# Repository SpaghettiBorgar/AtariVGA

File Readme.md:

# Atari to VGA Adapter
Converts VGA signals to the 13-pin DIN connector used by Atari SM/ST Series Monochrome CRT Monitors

## Features
- Adjustable R/G/B mixdown
- Adjustable output Attenuation/Amplification
- 3.5mm jack for audio passthrough
- VGA passthrough port
- 24C02 EEPROM for custom EDID
- Jumpers for SDA/SCL selection and write-protection
- Plenty of test-points for analyzing and debugging
- Blåhaj

> [!IMPORTANT]
> Some adapters will refuse to set a mode and send signals if it doesn't receive an EDID from the connected display. To provide an EDID you need to either connect a VGA monitor via the passthrough port or install and flash the 24C02 EEPROM with a valid EEPROM, preferably matching your monitor's specs as close as possible. Then use tools like `xrandr` to refine your VGA timings.

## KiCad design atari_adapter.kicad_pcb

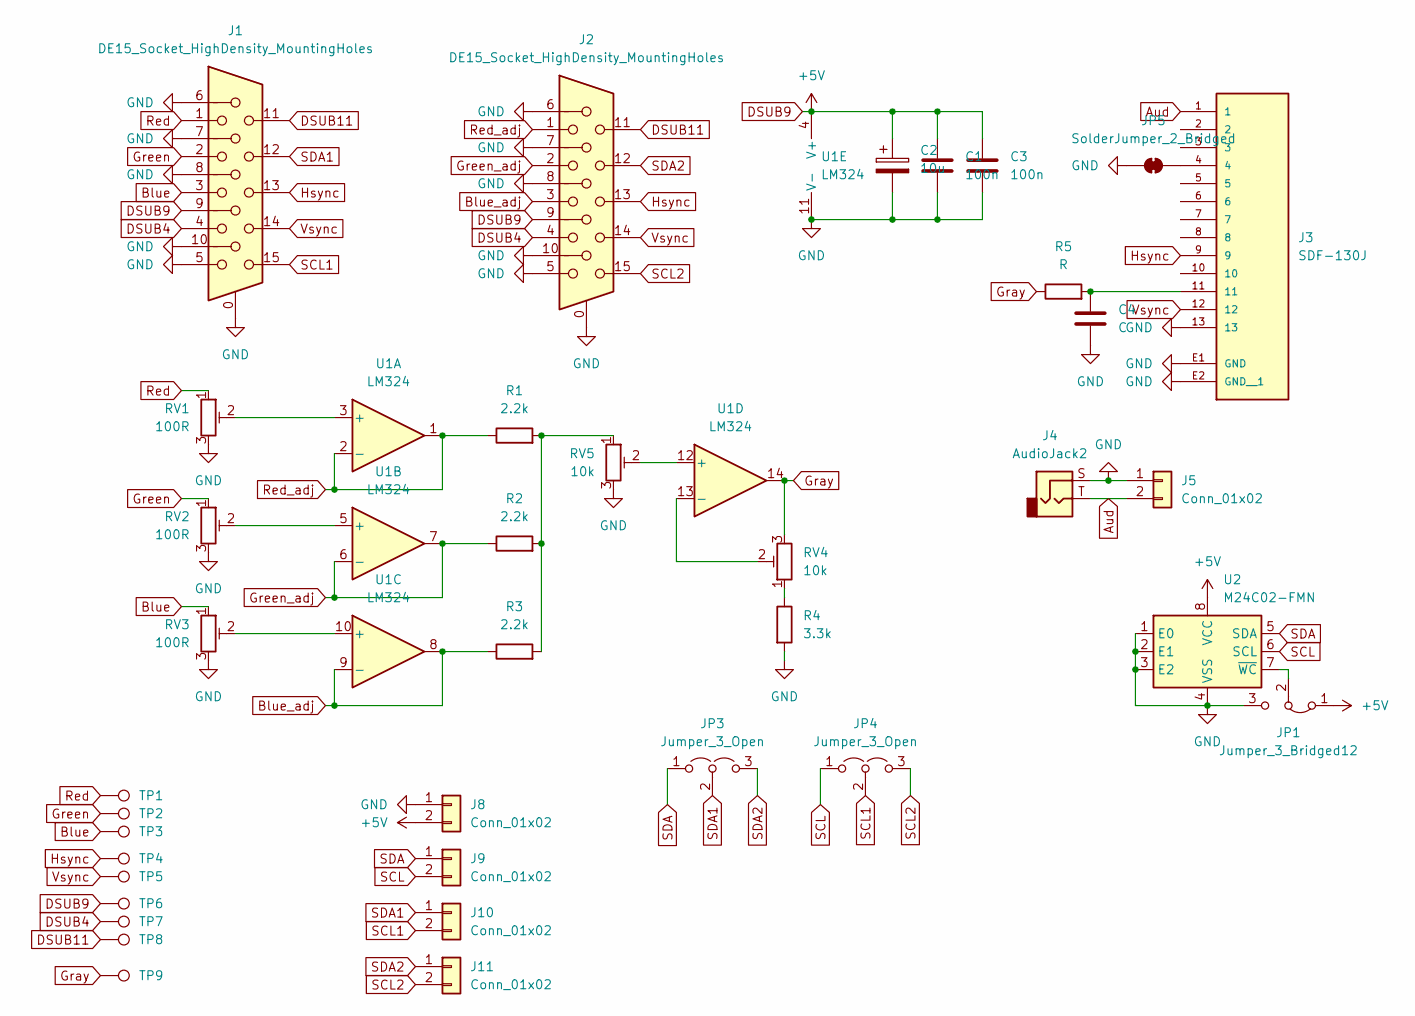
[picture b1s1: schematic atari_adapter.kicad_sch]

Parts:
C1, C3: 100n; C_1206_3216Metric_Pad1.33x1.80mm_HandSolder
C2: 10u; CP_Elec_4x5.4
C4: C; C_0805_2012Metric_Pad1.18x1.45mm_HandSolder
J1, J2: DE15_Socket_HighDensity_MountingHoles; DSUB-15-HD_Socket_Horizontal_P2.29x2.54mm_EdgePinOffset8.35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
J3: SDF-130J; CUI_SDF-130J; PARTREV 1.08/04-13-2020
J4: AudioJack2; Jack_3.5mm_CUI_SJ-3524-THT_Horizontal
J5, J8, J9, J10, J11: Conn_01x02; PinHeader_1x02_P2.54mm_Vertical
JP1: Jumper_3_Bridged12; PinHeader_1x03_P2.54mm_Vertical
JP3, JP4: Jumper_3_Open; PinHeader_1x03_P2.54mm_Vertical
JP5: SolderJumper_2_Bridged; SolderJumper-2_P1.3mm_Bridged_RoundedPad1.0x1.5mm
R1, R2, R3: 2.2k; R_0805_2012Metric_Pad1.20x1.40mm_HandSolder
R4: 3.3k; R_0805_2012Metric_Pad1.20x1.40mm_HandSolder
R5: R; R_0805_2012Metric_Pad1.20x1.40mm_HandSolder
RV1, RV2, RV3: 100R; Potentiometer_Runtron_RM-065_Vertical
RV4, RV5: 10k; Potentiometer_Runtron_RM-065_Vertical
TP1, TP2, TP3, TP4, TP5, TP6, TP7, TP8, TP9: TestPoint; Pin_D1.0mm_L10.0mm
U1: LM324; SOIC-14_3.9x8.7mm_P1.27mm
U2: M24C02-FMN; SOIC-8_3.9x4.9mm_P1.27mm

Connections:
Aud: J3.1, J4.T, J5.2
Blue: J1.3, RV3.1, TP3.1
Blue_adj: J2.3, R3.1, U1.8, U1.9 (-)
DSUB4: J1.4, J2.4, TP7.1
DSUB9: C1.1, C2.1, C3.1, J1.9, J2.9, J8.2, JP1.1 (A), TP6.1, U1.4 (V+), U2.8 (VCC)
DSUB11: J1.11, J2.11, TP8.1
GND: C1.2, C2.2, C3.2, C4.2, J1.0, J1.5, J1.6, J1.7, J1.8, J1.10, J2.0, J2.5, J2.6, J2.7, J2.8, J2.10, J3.13, J3.E1 (GND), J3.E2 (GND__1), J4.S, J5.1, J8.1, JP1.3 (B), JP5.1 (A), R4.2, RV1.3, RV2.3, RV3.3, RV5.3, U1.11 (V-), U2.1 (E0), U2.2 (E1), U2.3 (E2), U2.4 (VSS)
Gray: R5.1, RV4.3, TP9.1, U1.14
Green: J1.2, RV2.1, TP2.1
Green_adj: J2.2, R2.1, U1.6 (-), U1.7
Hsync: J1.13, J2.13, J3.9, TP4.1
unnamed: C4.1, J3.11, R5.2
unnamed: JP1.2 (C), U2.7 (~WC)
unnamed: J3.4, JP5.2 (B)
unnamed: R1.2, R2.2, R3.2, RV5.1
unnamed: R4.1, RV4.1
unnamed: RV1.2, U1.3 (+)
unnamed: RV2.2, U1.5 (+)
unnamed: RV3.2, U1.10 (+)
unnamed: RV5.2, U1.12 (+)
unnamed: RV4.2, U1.13 (-)
Red: J1.1, RV1.1, TP1.1
Red_adj: J2.1, R1.1, U1.1, U1.2 (-)
SCL: J9.2, JP4.1 (A), U2.6 (SCL)
SCL1: J1.15, J10.2, JP4.2 (C)
SCL2: J2.15, J11.2, JP4.3 (B)
SDA: J9.1, JP3.1 (A), U2.5 (SDA)
SDA1: J1.12, J10.1, JP3.2 (C)
SDA2: J2.12, J11.1, JP3.3 (B)
Vsync: J1.14, J2.14, J3.12, TP5.1

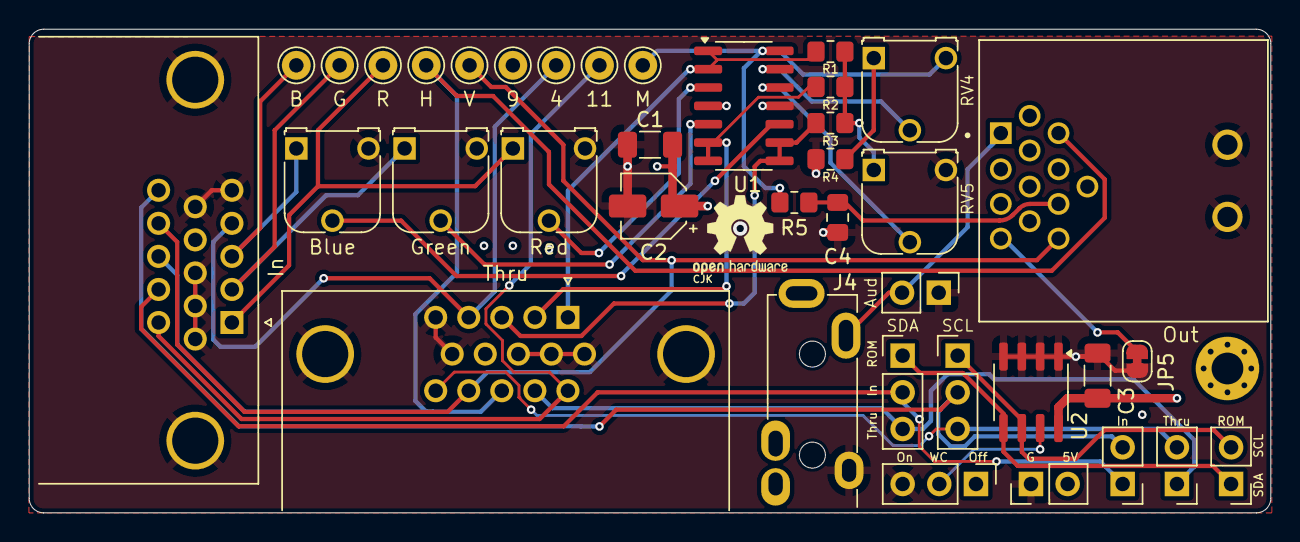
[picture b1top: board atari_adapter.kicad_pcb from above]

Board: 4 copper layers, 86.0 x 33.5 mm, 38 parts (0 on the bottom side), 30 nets.

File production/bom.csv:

Designator,Footprint,Quantity,Value,LCSC Part #
"C1, C3",1206,2,100n,
C2,CP_Elec_4x5.4,1,10u,
C4,0805,1,C,
"J1, J2",DSUB-15-HD_Socket_Horizontal_P2.29x2.54mm_EdgePinOffset8.35mm_Housed_MountingHolesOffset10.89mm,2,DE15_Socket_HighDensity_MountingHoles,
"J10, J11, J5, J8, J9",PinHeader_1x02_P2.54mm_Vertical,5,Conn_01x02,
J3,CUI_SDF-130J,1,SDF-130J,
J4,Jack_3.5mm_CUI_SJ-3524-THT_Horizontal,1,AudioJack2,
"R1, R2, R3",0805,3,2.2k,
R4,0805,1,3.3k,
R5,0805,1,R,
"RV1, RV2, RV3",Potentiometer_Runtron_RM-065_Vertical,3,100R,
"RV4, RV5",Potentiometer_Runtron_RM-065_Vertical,2,10k,
"TP1, TP2, TP3, TP4, TP5, TP6, TP7, TP8, TP9",Pin_D1.0mm_L10.0mm,9,TestPoint,
U1,SOIC-14_3.9x8.7mm_P1.27mm,1,LM324,
U2,SOIC-8_3.9x4.9mm_P1.27mm,1,M24C02-FMN,

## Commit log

2025-05-28 Revision 1 completed
2025-08-19 rm trash
2025-08-19 Add Readme
